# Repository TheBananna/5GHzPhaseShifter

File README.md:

# 5GHzPhaseShifter
 A 5GHz narrowband attenuator based vector summing phase shifter with two different attentuator types for evaluation purposes. This was never built or tested as I found a 1.7-2.2GHz option for cheaper. You will likely have to open the image in a new tab to resolve all of the detail.

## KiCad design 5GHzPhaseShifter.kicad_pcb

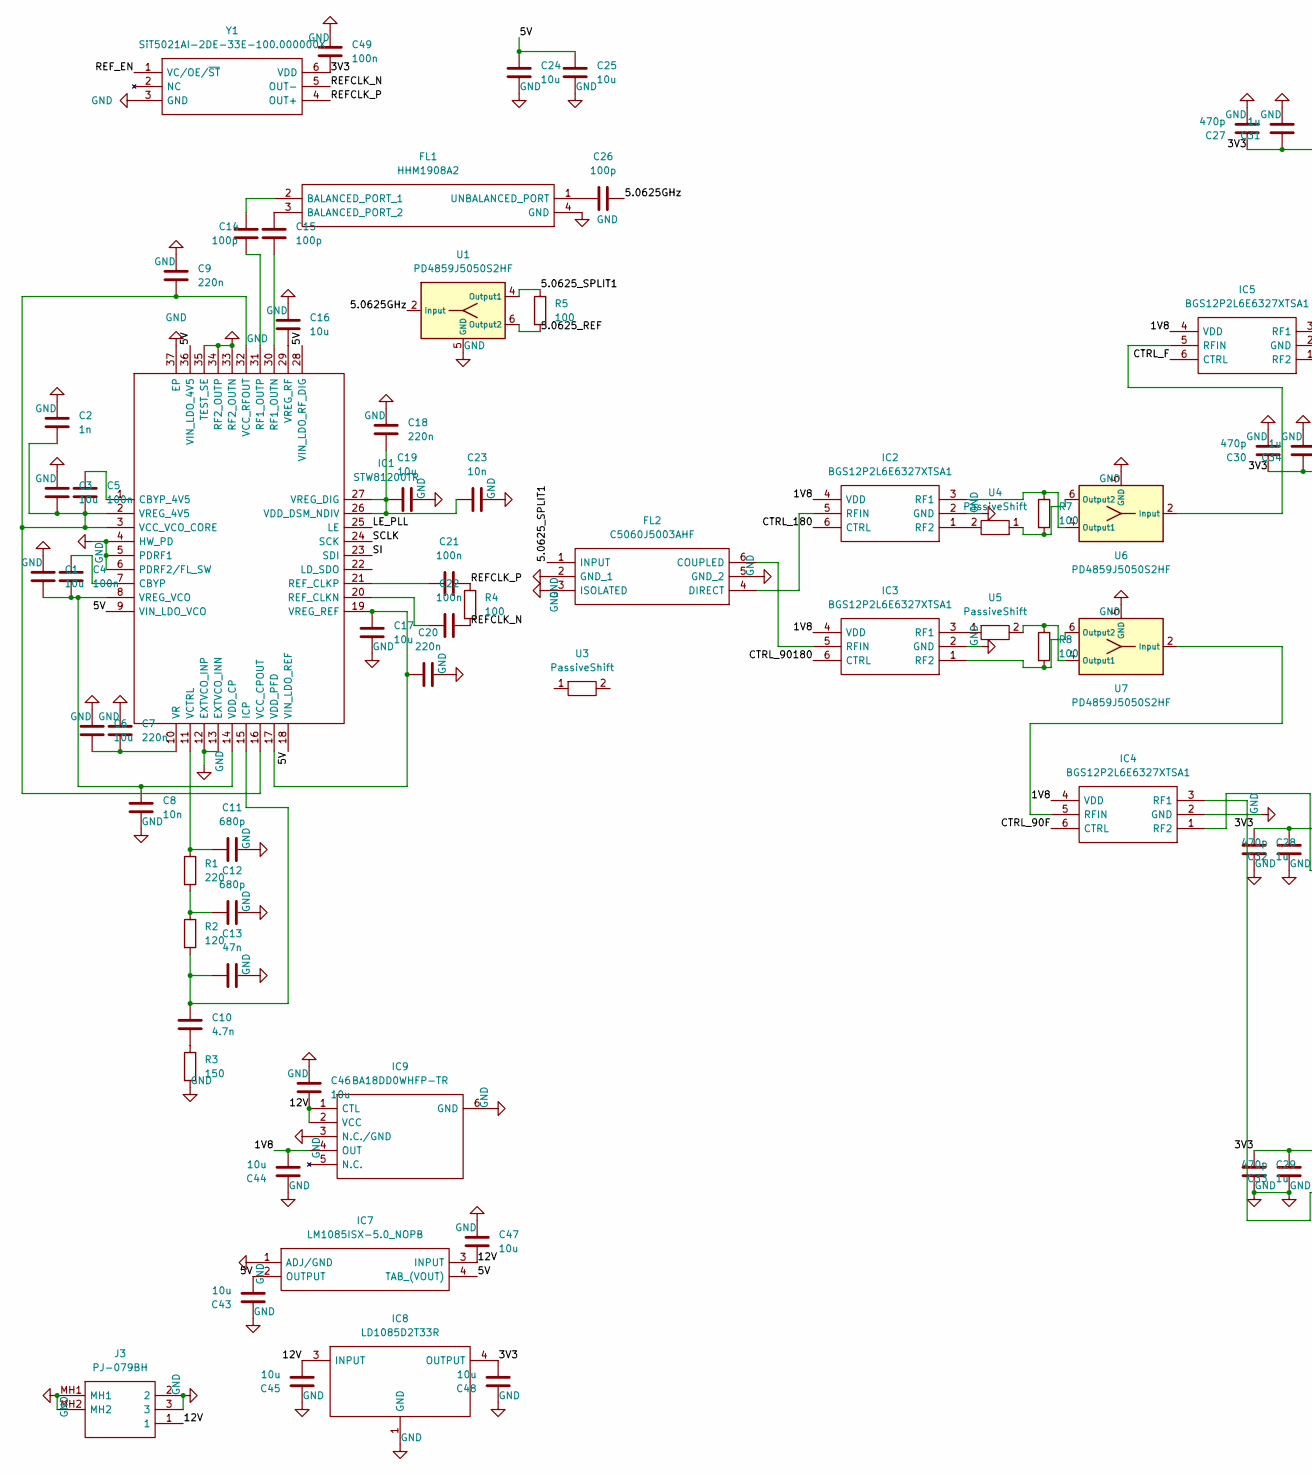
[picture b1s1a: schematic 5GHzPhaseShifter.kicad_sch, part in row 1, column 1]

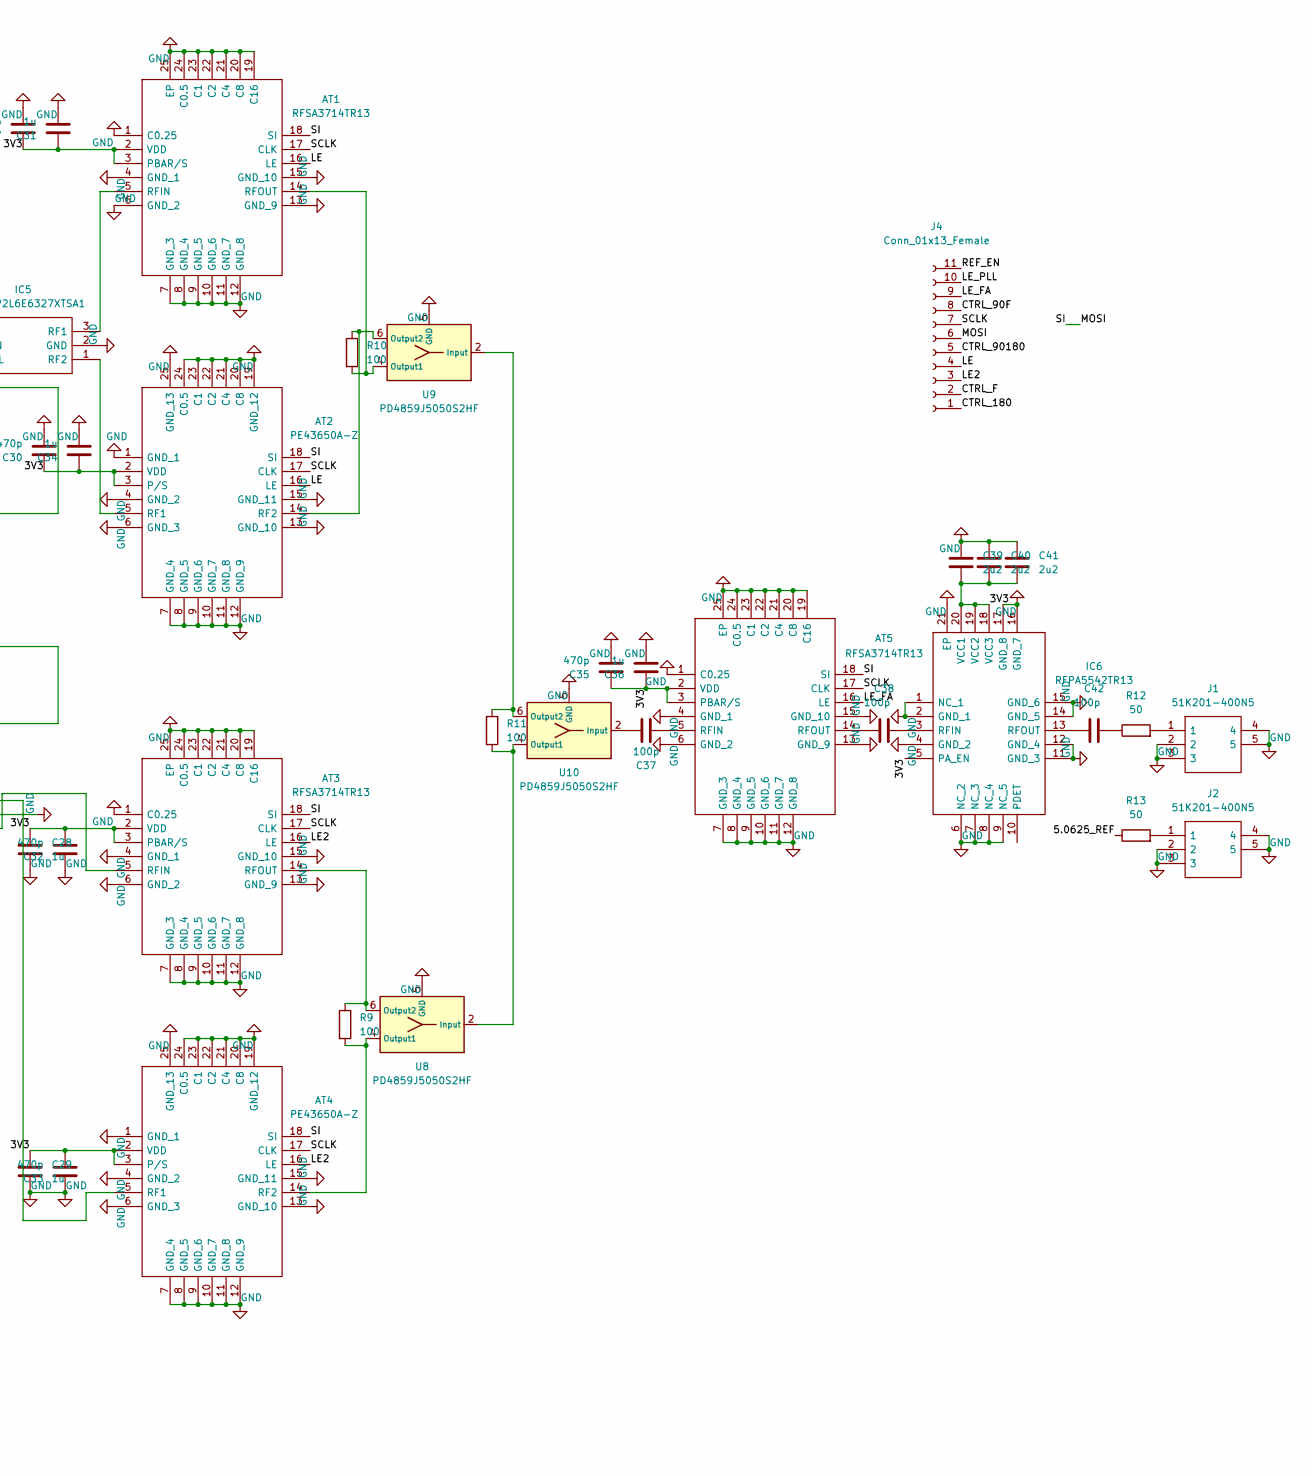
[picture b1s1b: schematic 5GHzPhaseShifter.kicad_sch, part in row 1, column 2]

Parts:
AT1, AT3, AT5: RFSA3714TR13; QFN50P400X400X90-25N-D; Mouser Part Number 772-RFSA3714
AT2, AT4: PE43650A-Z; QFN50P400X400X90-25N; Manufacturer_Part_Number PE43650A-Z
C1, C3, C6, C16, C17, C19, C24, C25, C43, C44, C45, C46, C47, C48: 10u; R_0603_1608Metric
C2: 1n; R_0402_1005Metric
C4, C5, C21, C22, C49: 100n; R_0402_1005Metric
C7, C9, C18, C20: 220n; R_0402_1005Metric
C8: 10n; R_0402_1005Metric
C10: 4.7n; R_0402_1005Metric
C11, C12: 680p; R_0402_1005Metric
C13: 47n; R_0402_1005Metric
C14, C15, C26, C37, C38, C42: 100p; R_0402_1005Metric
C23: 10n; R_0603_1608Metric
C27, C30, C32, C33, C35: 470p; R_0402_1005Metric
C28, C29, C31, C34, C36: 1u; R_0603_1608Metric
C39, C40, C41: 2u2; R_0603_1608Metric
FL1: HHM1908A2; Mouser Part Number 810-HHM1908A2
FL2: C5060J5003AHF; Mouser Part Number 620-C5060J5003AHF
IC1: STW81200TR; QFN50P600X600X100-37N-D; Mouser Part Number 511-STW81200TR
IC2, IC3, IC4, IC5: BGS12P2L6E6327XTSA1; Mouser Part Number 726-BGS12P2L6E6327XT
IC6: RFPA5542TR13; QFN50P400X400X90-21N-D; Mouser Part Number 772-RFPA5542TR13
IC7: LM1085ISX-5.0_NOPB; KTT0003B; Mouser Part Number 926-LM1085ISX50NOPB
IC8: LD1085D2T33R; Mouser Part Number 511-LD1085D2T33-TR
IC9: BA18DD0WHFP-TR; BA18DD0WHFPTR; Mouser Part Number 755-BA18DD0WHFP-TR
J1, J2: 51K201-400N5; 51K201400N5; Mouser Part Number 476-51K201-400N5
J3: PJ-079BH; PJ079BH; Mouser Part Number 490-PJ-079BH
J4: Conn_01x13_Female; PinHeader_1x11_P2.54mm_Vertical
R1: 220; R_0402_1005Metric
R2: 120; R_0402_1005Metric
R3: 150; R_0402_1005Metric
R4: 100; R_0402_1005Metric
R5, R7, R8, R9, R10, R11: 100; R_0603_1608Metric
R12, R13: 50; R_0402_1005Metric
U1, U6, U7, U8, U9, U10: PD4859J5050S2HF; Anaren_0805_2012Metric-6
U3: PassiveShift; 90Shift_5.0625GHz
U4, U5: PassiveShift; 180Shift_5.0625GHz
Y1: SiT5021AI-2DE-33E-100.000000X; SiT5021AI2DE33E100000000X; Mouser Part Number 788-1AI-2DE-3E-100X

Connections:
/1V8: C44.1, IC2.4 (VDD), IC3.4 (VDD), IC4.4 (VDD), IC5.4 (VDD), IC9.4 (OUT)
/3V3: AT1.2 (VDD), AT1.3 (PBAR/S), AT2.2 (VDD), AT2.3 (P/S), AT3.2 (VDD), AT3.3 (PBAR/S), AT4.2 (VDD), AT4.3 (P/S), AT5.2 (VDD), AT5.3 (PBAR/S), C27.1, C28.1, C29.1, C30.1, C31.1, C32.2, C33.2, C34.1, C35.1, C36.1, C39.1, C40.2, C41.2, C48.1, C49.1, IC6.5 (PA_EN), IC6.18 (VCC3), IC6.19 (VCC2), IC6.20 (VCC1), IC8.4 (OUTPUT), Y1.6 (VDD)
/5.0625GHz: C26.1, U1.2 (Input)
/5.0625_REF: R5.2, R13.1, U1.6 (Output2)
/5.0625_SPLIT1: FL2.1 (INPUT), R5.1, U1.4 (Output1)
/5V: C24.1, C25.1, C43.1, IC1.9 (VIN_LDO_VCO), IC1.18 (VIN_LDO_REF), IC1.28 (VIN_LDO_RF_DIG), IC1.36 (VIN_LDO_4V5), IC7.2 (OUTPUT), IC7.4 (TAB_(VOUT))
/12V: C45.1, C46.1, C47.1, IC7.3 (INPUT), IC8.3 (INPUT), IC9.1 (CTL), IC9.2 (VCC), J3.1
/CTRL_90F: IC4.6 (CTRL), J4.8
/CTRL_180: IC2.6 (CTRL), J4.1
/CTRL_90180: IC3.6 (CTRL), J4.5
/CTRL_F: IC5.6 (CTRL), J4.2
/LE: AT1.16 (LE), AT2.16 (LE), J4.4
/LE2: AT3.16 (LE), AT4.16 (LE), J4.3
/LE_FA: AT5.16 (LE), J4.9
/LE_PLL: IC1.25 (LE), J4.10
/MOSI: AT1.18 (SI), AT2.18 (SI), AT3.18 (SI), AT4.18 (SI), AT5.18 (SI), IC1.23 (SDI), J4.6
/REFCLK_N: C22.1, R4.2, Y1.5 (OUT-)
/REFCLK_P: C21.2, R4.1, Y1.4 (OUT+)
/REF_EN: J4.11, Y1.1 (VC/OE/~ST)
/SCLK: AT1.17 (CLK), AT2.17 (CLK), AT3.17 (CLK), AT4.17 (CLK), AT5.17 (CLK), IC1.24 (SCK), J4.7
GND: AT1.1 (C0.25), AT1.4 (GND_1), AT1.6 (GND_2), AT1.7 (GND_3), AT1.8 (GND_4), AT1.9 (GND_5), AT1.10 (GND_6), AT1.11 (GND_7), AT1.12 (GND_8), AT1.13 (GND_9), AT1.15 (GND_10), AT1.19 (C16), AT1.20 (C8), AT1.21 (C4), AT1.22 (C2), AT1.23 (C1), AT1.24 (C0.5), AT1.25 (EP), AT2.1 (GND_1), AT2.4 (GND_2), AT2.6 (GND_3), AT2.7 (GND_4), AT2.8 (GND_5), AT2.9 (GND_6), AT2.10 (GND_7), AT2.11 (GND_8), AT2.12 (GND_9), AT2.13 (GND_10), AT2.15 (GND_11), AT2.19 (GND_12), AT2.20 (C8), AT2.21 (C4), AT2.22 (C2), AT2.23 (C1), AT2.24 (C0.5), AT2.25 (GND_13), AT3.1 (C0.25), AT3.4 (GND_1), AT3.6 (GND_2), AT3.7 (GND_3), AT3.8 (GND_4), AT3.9 (GND_5), AT3.10 (GND_6), AT3.11 (GND_7), AT3.12 (GND_8), AT3.13 (GND_9), AT3.15 (GND_10), AT3.19 (C16), AT3.20 (C8), AT3.21 (C4), AT3.22 (C2), AT3.23 (C1), AT3.24 (C0.5), AT3.25 (EP), AT4.1 (GND_1), AT4.4 (GND_2), AT4.6 (GND_3), AT4.7 (GND_4), AT4.8 (GND_5), AT4.9 (GND_6), AT4.10 (GND_7), AT4.11 (GND_8), AT4.12 (GND_9), AT4.13 (GND_10), AT4.15 (GND_11), AT4.19 (GND_12), AT4.20 (C8), AT4.21 (C4), AT4.22 (C2), AT4.23 (C1), AT4.24 (C0.5), AT4.25 (GND_13), AT5.1 (C0.25), AT5.4 (GND_1), AT5.6 (GND_2), AT5.7 (GND_3), AT5.8 (GND_4), AT5.9 (GND_5), AT5.10 (GND_6), AT5.11 (GND_7), AT5.12 (GND_8), AT5.13 (GND_9), AT5.15 (GND_10), AT5.19 (C16), AT5.20 (C8), AT5.21 (C4), AT5.22 (C2), AT5.23 (C1), AT5.24 (C0.5), AT5.25 (EP), C1.2, C2.2, C3.2, C6.2, C7.2, C8.2, C9.2, C11.2, C12.2, C13.2, C16.2, C17.2, C18.2, C19.2, C20.2, C23.2, C24.2, C25.2, C27.2, C28.2, C29.2, C30.2, C31.2, C32.1, C33.1, C34.2, C35.2, C36.2, C39.2, C40.1, C41.1, C43.2, C44.2, C45.2, C46.2, C47.2, C48.2, C49.2, FL1.4 (GND), FL2.2 (GND_1), FL2.3 (ISOLATED), FL2.5 (GND_2), IC1.4 (HW_PD), IC1.5 (PDRF1), IC1.6 (PDRF2/FL_SW), IC1.12 (EXTVCO_INP), IC1.13 (EXTVCO_INN), IC1.33 (RF2_OUTN), IC1.34 (RF2_OUTP), IC1.35 (TEST_SE), IC1.37 (EP), IC2.2 (GND), IC3.2 (GND), IC4.2 (GND), IC5.2 (GND), IC6.1 (NC_1), IC6.2 (GND_1), IC6.4 (GND_2), IC6.6 (NC_2), IC6.7 (NC_3), IC6.8 (NC_4), IC6.9 (NC_5), IC6.11 (GND_3), IC6.12 (GND_4), IC6.14 (GND_5), IC6.15 (GND_6), IC6.16 (GND_7), IC6.17 (GND_8), IC6.21 (EP), IC7.1 (ADJ/GND), IC8.1 (GND), IC9.3 (N.C./GND), IC9.6 (GND), J1.2, J1.3, J1.4, J1.5, J2.2, J2.3, J2.4, J2.5, J3.2, J3.3, J3.MH1, J3.MH2, R3.2, U1.1,3,5 (GND), U1.5 (GND), U6.1,3,5 (GND), U6.5 (GND), U7.1,3,5 (GND), U7.5 (GND), U8.1,3,5 (GND), U8.5 (GND), U9.1,3,5 (GND), U9.5 (GND), U10.1,3,5 (GND), U10.5 (GND), Y1.3 (GND)
unnamed: AT1.5 (RFIN), IC5.3 (RF1)
unnamed: AT1.14 (RFOUT), R10.2, U9.4 (Output1)
unnamed: AT2.5 (RF1), IC5.1 (RF2)
unnamed: AT2.14 (RF2), R10.1, U9.6 (Output2)
unnamed: AT3.5 (RFIN), IC4.1 (RF2)
unnamed: AT3.14 (RFOUT), R9.1, U8.6 (Output2)
unnamed: AT4.5 (RF1), IC4.3 (RF1)
unnamed: AT4.14 (RF2), R9.2, U8.4 (Output1)
unnamed: AT5.5 (RFIN), C37.1
unnamed: AT5.14 (RFOUT), C38.2
unnamed: C1.1, C4.1, C8.1, IC1.8 (VREG_VCO), IC1.14 (VDD_CP)
unnamed: C2.1, C3.1, C5.1, C9.1, IC1.2 (VREG_4V5), IC1.3 (VCC_VCO_CORE), IC1.16 (VCC_CPOUT), IC1.32 (VCC_RFOUT)
unnamed: C4.2, IC1.7 (CBYP)
unnamed: C5.2, IC1.1 (CBYP_4V5)
unnamed: C6.1, C7.1, IC1.10 (VR)
unnamed: C10.1, R3.1
unnamed: C10.2, C13.1, IC1.15 (ICP), R2.2
unnamed: C11.1, IC1.11 (VCTRL), R1.1
unnamed: C12.1, R1.2, R2.1
unnamed: C14.1, IC1.31 (RF1_OUTP)
unnamed: C14.2, FL1.2 (BALANCED_PORT_1)
unnamed: C15.1, IC1.30 (RF1_OUTN)
unnamed: C15.2, FL1.3 (BALANCED_PORT_2)
unnamed: C16.1, IC1.29 (VREG_RF)
unnamed: C17.1, C20.1, IC1.17 (VDD_PFD), IC1.19 (VREG_REF)
unnamed: C18.1, C19.1, C23.1, IC1.26 (VDD_DSM_NDIV), IC1.27 (VREG_DIG)
unnamed: C21.1, IC1.21 (REF_CLKP)
unnamed: C22.2, IC1.20 (REF_CLKN)
unnamed: C26.2, FL1.1 (UNBALANCED_PORT)
unnamed: C37.2, U10.2 (Input)
unnamed: C38.1, IC6.3 (RFIN)
unnamed: C42.1, R12.1
unnamed: C42.2, IC6.13 (RFOUT)
unnamed: IC2.1 (RF2), U4.2
unnamed: IC2.3 (RF1), R7.1, U6.4 (Output1)
unnamed: FL2.4 (DIRECT), IC2.5 (RFIN)
unnamed: IC3.1 (RF2), R8.2, U7.6 (Output2)
unnamed: IC3.3 (RF1), U5.1
unnamed: FL2.6 (COUPLED), IC3.5 (RFIN)
unnamed: IC4.5 (RFIN), U7.2 (Input)
unnamed: IC5.5 (RFIN), U6.2 (Input)
unnamed: J1.1, R12.2
unnamed: J2.1, R13.2
unnamed: R7.2, U4.1, U6.6 (Output2)
unnamed: R8.1, U5.2, U7.4 (Output1)
unnamed: R11.1, U9.2 (Input), U10.6 (Output2)
unnamed: R11.2, U8.2 (Input), U10.4 (Output1)

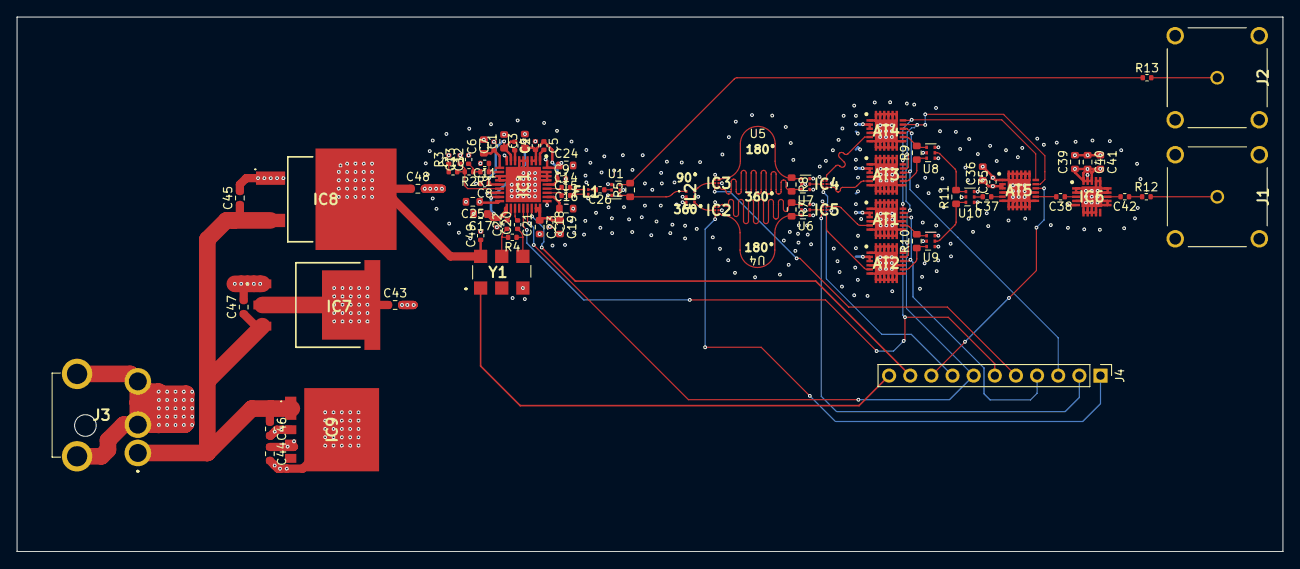
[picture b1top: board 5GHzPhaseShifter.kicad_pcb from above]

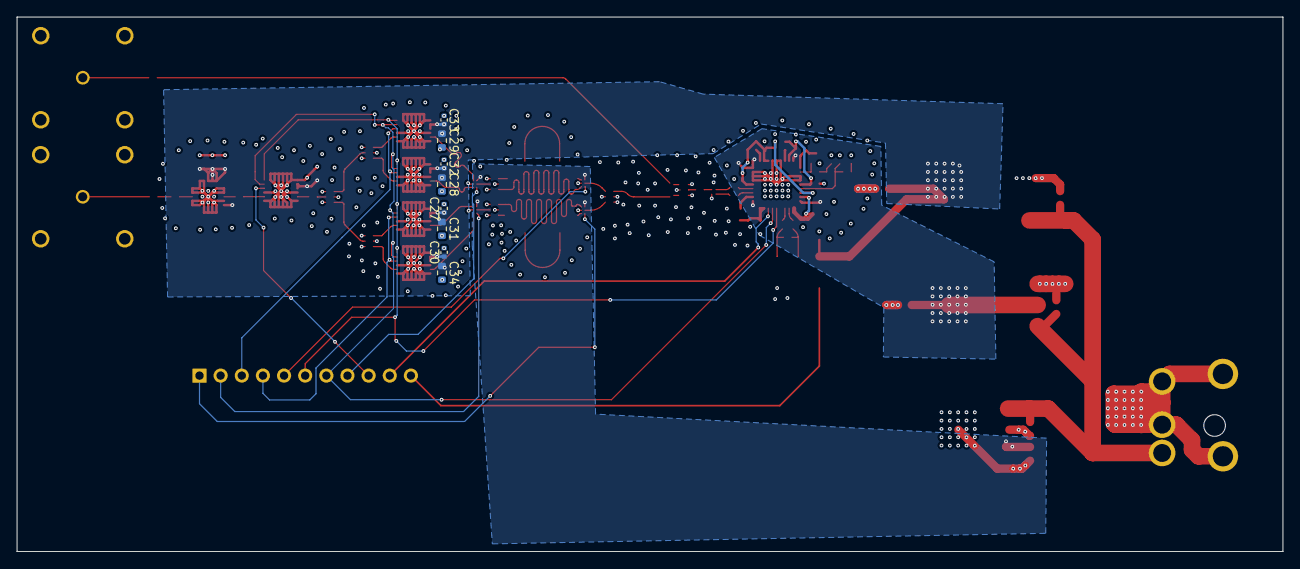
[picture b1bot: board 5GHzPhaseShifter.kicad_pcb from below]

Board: 4 copper layers, 152.1 x 64.2 mm, 90 parts (8 on the bottom side), 68 nets.
